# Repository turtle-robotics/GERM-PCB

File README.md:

# GERM PCB
## Intro
- This repository holds all the PCB information to allow for seamless syncing between team members who want to work on the design for GERM
- The design files for this project are built from **KiCAD**, and is what we will be using throughout the remainder of the project

## Design
- Design choices for this PCB are per the documentation in the [Drive](https://drive.google.com/drive/u/0/folders/1dtvyD7S52Tu-Nz1_2z5B_uvttlOJOdOd)

## Setup
1. Install **KiCAD 10** and **git**
2. Make sure you have been added to the `turtle-robotics` GitHub repo with write access, and that your SSH key is added to your GitHub account
3. Clone the repo:
   ```
   git clone git@github.com:turtle-robotics/GERM-PCB.git
   ```
   (Or use **File → Clone Project from Repository** in KiCAD and paste the repo link)
4. Open `GERM_PCB.kicad_pro` from the cloned folder in KiCAD
5. That's it!

## Pulling (getting the latest changes)
Nothing syncs automatically. Pull **before you start working**, and any time you want your teammates' latest changes:
```
cd GERM-PCB
git pull
```
Close KiCAD's editors before pulling if you have unsaved changes, then reopen the project afterwards so it loads the new files.

## Pushing (sharing your changes)
When you are done with a work session, save in KiCAD, close it, then run:
```
git add -A
git commit -m "short description of what you changed"
git push
```
If the push is rejected, someone pushed before you. Run `git pull --rebase` and then `git push` again.

## Avoiding conflicts
KiCAD files are text, but two people editing the same file at once cause merge conflicts that are painful to fix by hand.
- Agree on who is editing which file or schematic sheet before starting
- Always pull before you start and push when you stop
- Don't leave your changes unpushed for days

## What is (and isn't) in the repo
- Tracked: `.kicad_pro`, `.kicad_sch`, `.kicad_pcb`, `fp-lib-table`, and the custom footprint library folders (`*.pretty`)
- Ignored (see `.gitignore`): `.history/` (KiCAD's local backups), `*.lck` lock files, `*-backups/`, and `fp-info-cache`

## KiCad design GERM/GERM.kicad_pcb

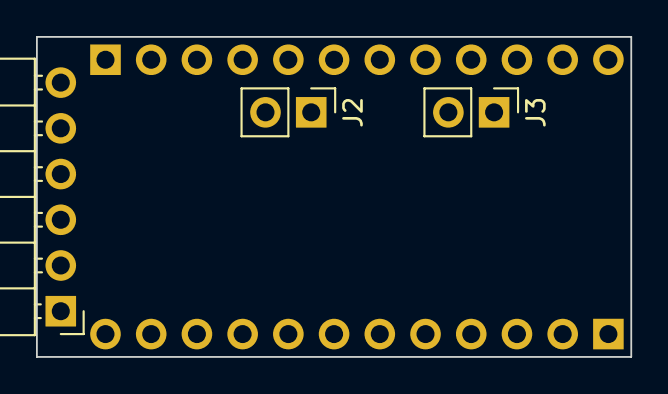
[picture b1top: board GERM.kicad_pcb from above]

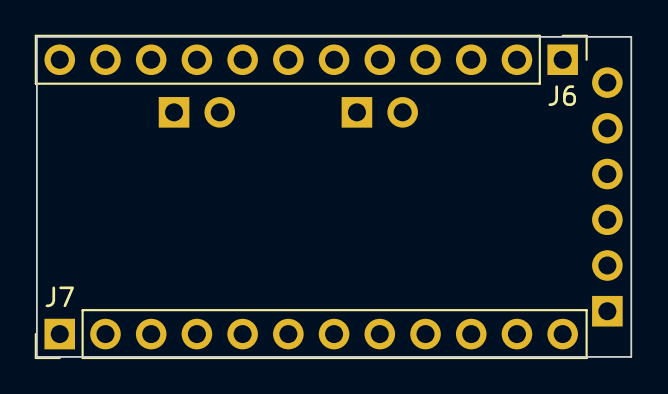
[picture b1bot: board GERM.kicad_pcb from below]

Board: 2 copper layers, 33.0 x 17.8 mm, 5 parts (2 on the bottom side), 5 nets, no tracks yet.

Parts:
J1: FTDI; PinHeader_1x06_P2.54mm_Horizontal
J2: I2C; PinHeader_1x02_P2.54mm_Vertical
J3: Analog; PinHeader_1x02_P2.54mm_Vertical
J6: Analog; PinHeader_1x12_P2.54mm_Vertical
J7: Digital; PinHeader_1x12_P2.54mm_Vertical

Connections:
/RX: J1.4, J7.11
/TX: J1.5, J7.12
/~RESET: J6.3, J7.10
GND: J1.1, J1.2, J6.2, J7.9
VCC: J1.3, J6.4
